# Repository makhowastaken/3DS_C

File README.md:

# 3DS_C
USB Type C conversion board for original 3DS consoles

INSTALL AT YOUR OWN RISK!

These worked perfectly fine for me but I have had several reports of blown fuses. The parts are extremely close together and at very high risk of short with improper handling or install. Consider omitting the pads for the dock charger. The wider USB C port makes clearance very tight and without proper insulation, the pad WILL short on the body (ground) of the port. Again, it worked for me but it's really tight. 

---

You can order some boards [from ohspark here](https://oshpark.com/shared_projects/H7cVX6ow) or use the supplied gerber file zip to upload to your preferred fab (does use castellated holes). I tested this successfully with 0.8mm PCBs

Otherwise all you need are the USB Type C ports: [Aliexpress](https://www.aliexpress.com/item/32885941456.html) or [LCSC](https://lcsc.com/product-detail/USB-Connectors_XKB-Connectivity-U262-061N-4BVC11_C2764612.html)

And two optional (for Type C Host charging only) 5.1k 0603 resistors. 

For install, you will need to completely desolder the original port and file out the opening with needle files as the type C port is bigger than the OEM charge port. Solder the port to the new board, solder the optional resistors, then solder the board to the 3DS. I have also included pads to transplant the original pads for the dock charger but due to the size of the type C port, it's not recommended. See my install below for more info or better instruction. 

YouTube install: https://www.youtube.com/watch?v=8TaaZng31x4

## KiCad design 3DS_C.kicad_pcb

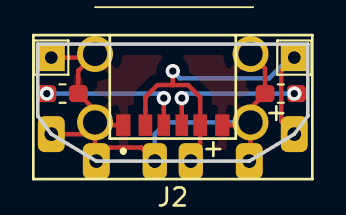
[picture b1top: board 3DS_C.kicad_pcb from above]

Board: 2 copper layers, 15.0 x 6.5 mm, 6 parts (0 on the bottom side), 4 nets.

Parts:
J1: TYPE-C-31-M-17; TYPEC31M17
J2: 3DS_POWER
R1, R2: 5.1K; R_0603_1608Metric_Pad1.05x0.95mm_HandSolder
VCC: VCC; TestPoint_THTPad_1.5x1.5mm_Drill0.7mm
VCC#2: VCC; TestPoint_THTPad_1.5x1.5mm_Drill0.7mm

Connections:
CC1: J1.A5, R1.1
CC2: J1.B5, R2.1
GND: J1.A12, J1.B12, J1.MH1, J1.MH2, J1.MH3, J1.MH4, J2.2, R1.2, R2.2, VCC.1
VCC: J1.A9, J1.B9, J2.1, VCC#2.1
